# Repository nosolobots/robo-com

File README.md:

# robo-com
 
The aim of the project is to create basic robotic kits for contests and competitions. 
 
Currently, there are two kits in progress: 
 
> **linus_v1** a *line follower* robot  
> **taurus_v1** a *mini sumo* robot

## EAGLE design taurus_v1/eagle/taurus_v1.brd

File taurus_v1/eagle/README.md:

### *taurus_v1* PCB eagle files repository

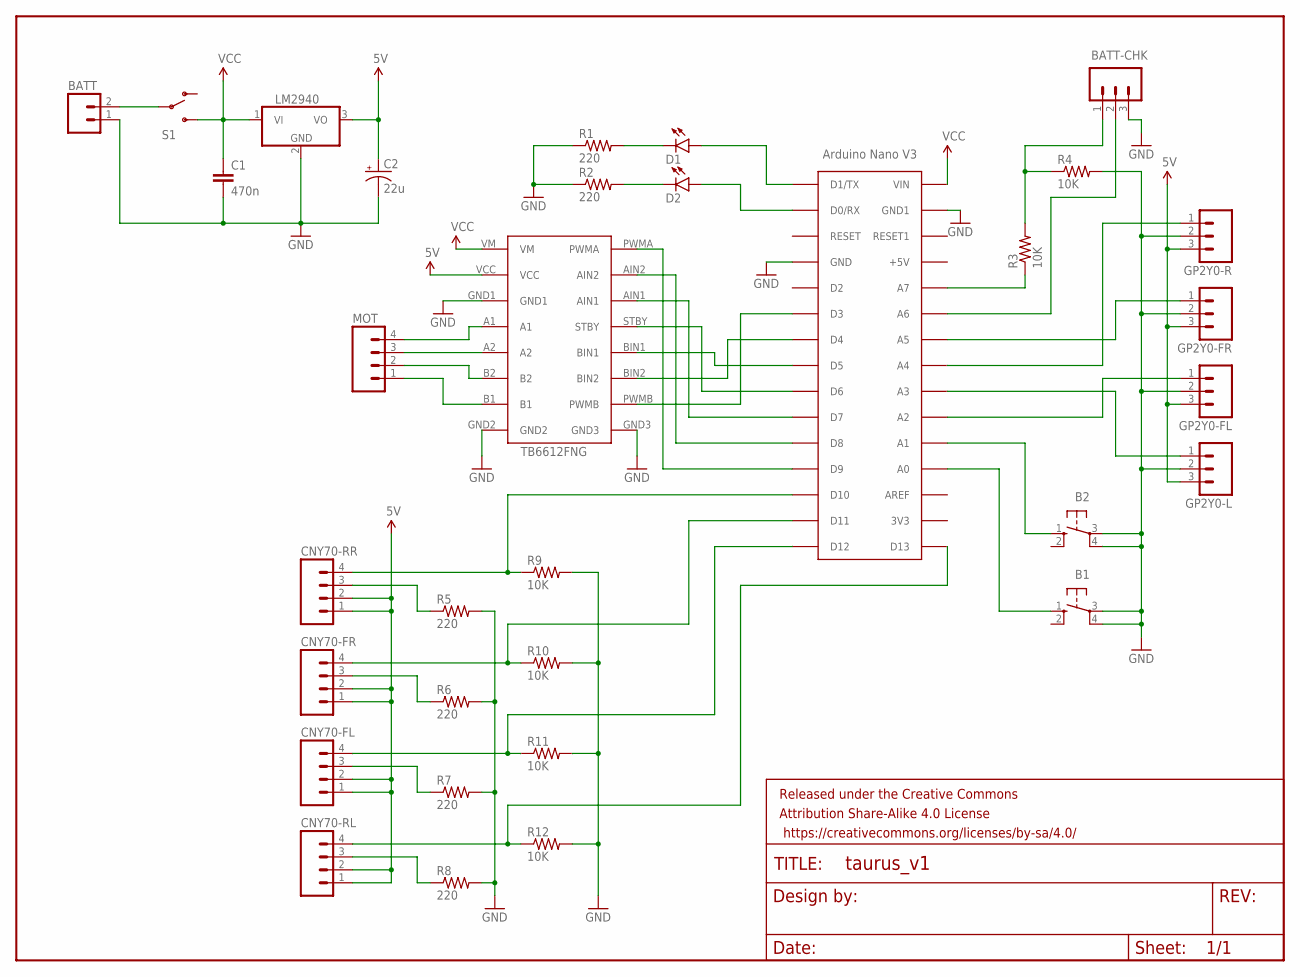
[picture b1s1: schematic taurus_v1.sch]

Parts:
B1, B2: 10-XX; B3F-10XX
BATT: M02PTH; 1X02
BATT-CHK: M03PTH; 1X03
C1: 470n; CAP-PTH-5MM
C2: 22u; CPOL-RADIAL-10UF-25V
CNY70-FL, CNY70-FR, CNY70-RL, CNY70-RR: M04PTH; 1X04
D1, D2: LED3MM
FRAME1: FRAME-LETTERNO_PACKAGE; DUMMY
GP2Y0-FL, GP2Y0-FR, GP2Y0-L, GP2Y0-R: M03PTH; 1X03
LM2940: 7805TV; TO220V
MOT: M04PTH; 1X04
R1, R2, R5, R6, R7, R8: 220; AXIAL-0.4
R3, R4, R9, R10, R11, R12: 10K; AXIAL-0.4
S1: SWITCH-SPDTPTH; SWITCH-SPDT
TB1: TB6612FNG
U$1: ARDUINONANO; PDIP-32

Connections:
5V: C2.1 (+), CNY70-FL.1, CNY70-FL.2, CNY70-FR.1, CNY70-FR.2, CNY70-RL.1, CNY70-RL.2, CNY70-RR.1, CNY70-RR.2, GP2Y0-FL.3, GP2Y0-FR.3, GP2Y0-L.3, GP2Y0-R.3, LM2940.3 (VO), TB1.VCC
GND: B1.3, B1.4 (P1), B2.3, B2.4 (P1), BATT.1, BATT-CHK.3, C1.2, C2.2 (-), GP2Y0-FL.2, GP2Y0-FR.2, GP2Y0-L.2, GP2Y0-R.2, LM2940.2 (GND), R1.P$1 (1), R2.P$1 (1), R4.P$2 (2), R5.P$2 (2), R6.P$2 (2), R7.P$2 (2), R8.P$2 (2), R9.P$2 (2), R10.P$2 (2), R11.P$2 (2), R12.P$2 (2), TB1.GND1, TB1.GND2, TB1.GND3, U$1.GND, U$1.GND1
unnamed: TB1.PWMA, U$1.D9
unnamed: TB1.AIN2, U$1.D8
unnamed: TB1.AIN1, U$1.D7
unnamed: TB1.STBY, U$1.D6
unnamed: TB1.BIN1, U$1.D5
unnamed: TB1.BIN2, U$1.D4
unnamed: TB1.PWMB, U$1.D3
unnamed: D1.K (C), R1.P$2 (2)
unnamed: D2.K (C), R2.P$2 (2)
unnamed: D2.A, U$1.D0/RX
unnamed: D1.A, U$1.D1/TX
unnamed: BATT.2, S1.2
unnamed: B1.1 (S), U$1.A7 (A0)
unnamed: B2.1 (S), U$1.A6 (A1)
unnamed: GP2Y0-L.1, U$1.A4 (A3)
unnamed: GP2Y0-R.1, U$1.A3 (A4)
unnamed: GP2Y0-FL.1, U$1.A5 (A2)
unnamed: BATT-CHK.2, U$1.A1 (A6)
unnamed: R3.P$1 (1), U$1.A0 (A7)
unnamed: BATT-CHK.1, R3.P$2 (2), R4.P$1 (1)
unnamed: MOT.4, TB1.A1
unnamed: MOT.3, TB1.A2
unnamed: MOT.2, TB1.B2
unnamed: MOT.1, TB1.B1
unnamed: CNY70-RR.4, R9.P$1 (1), U$1.D10
unnamed: CNY70-RR.3, R5.P$1 (1)
unnamed: CNY70-FR.3, R6.P$1 (1)
unnamed: CNY70-FL.3, R7.P$1 (1)
unnamed: CNY70-RL.3, R8.P$1 (1)
unnamed: CNY70-FR.4, R10.P$1 (1), U$1.D11
unnamed: CNY70-RL.4, R12.P$1 (1), U$1.D13
unnamed: CNY70-FL.4, R11.P$1 (1), U$1.D12
unnamed: GP2Y0-FR.1, U$1.A2 (A5)
VCC: C1.1, LM2940.1 (VI), S1.3 (S), TB1.VM, U$1.VIN

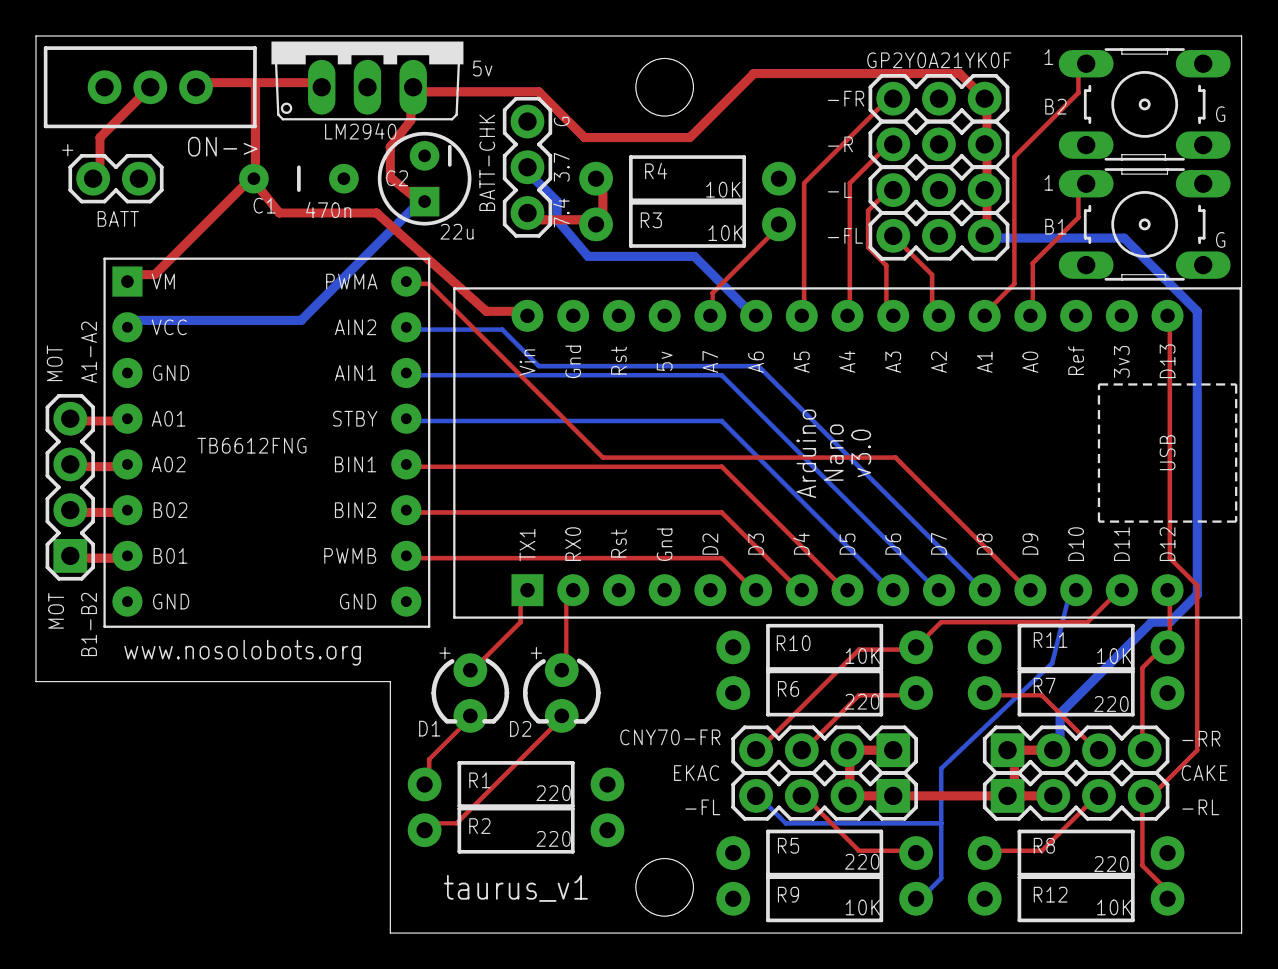
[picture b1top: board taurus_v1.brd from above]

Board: 2 copper layers, 67.0 x 49.8 mm, 34 parts (0 on the bottom side), 36 nets.

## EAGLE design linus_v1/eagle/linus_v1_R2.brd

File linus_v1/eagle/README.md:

### linus_v1 PCB eagle files repository

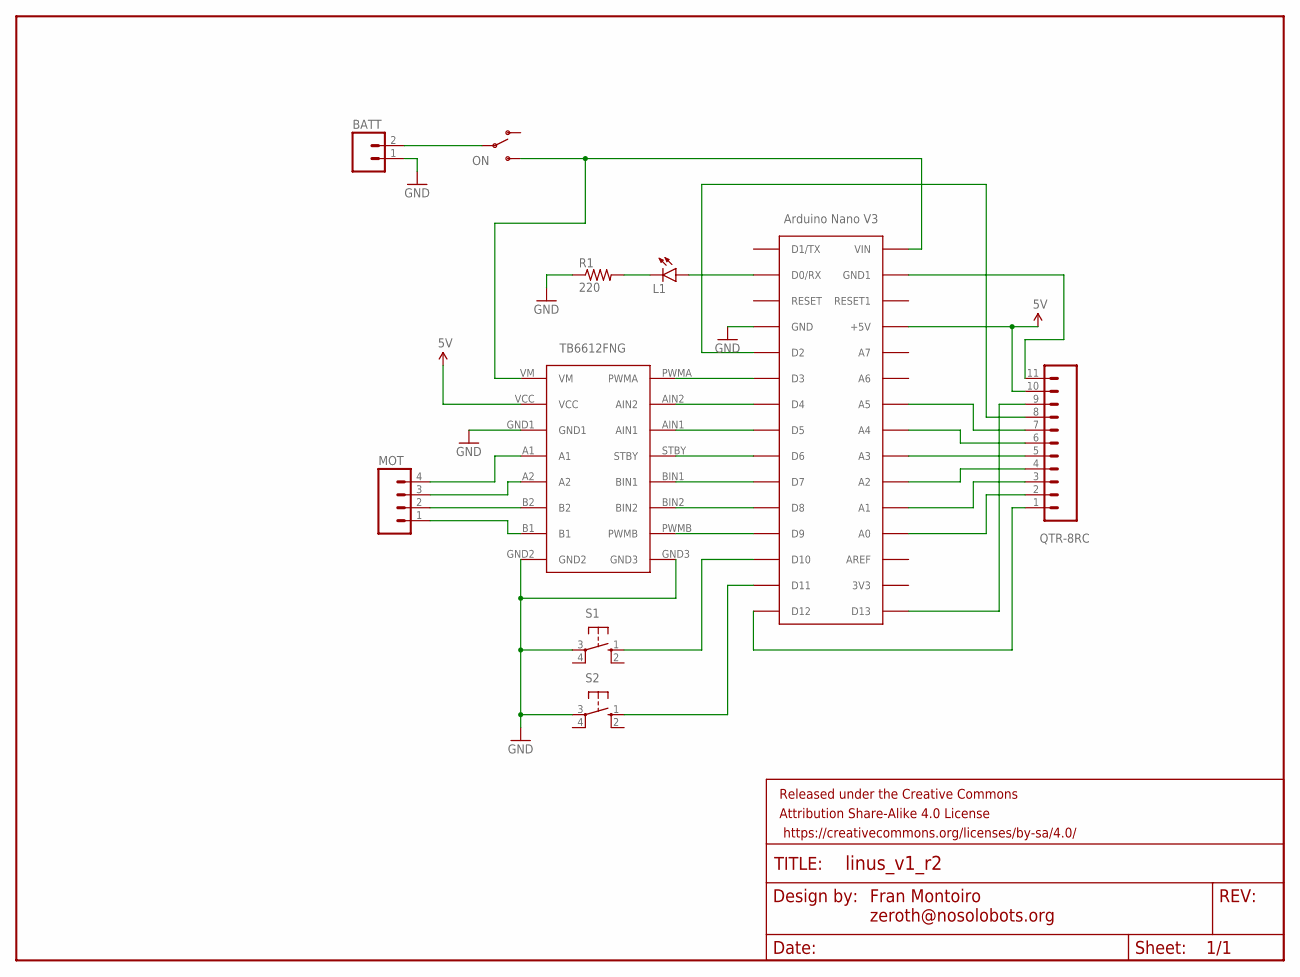
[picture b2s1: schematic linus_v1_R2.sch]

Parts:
BATT: M02PTH; 1X02
FRAME1: FRAME-LETTERNO_PACKAGE; DUMMY
L1: LED5MM
MOT: M04PTH; 1X04
ON: SWITCH-SPDTPTH; SWITCH-SPDT
QTR-8RC: M11PTH; 1X11
R1: 220; AXIAL-0.4
S1, S2: 10-XX; B3F-10XX
TB1: TB6612FNG
U$1: ARDUINONANO; PDIP-32

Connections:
5V: QTR-8RC.10, TB1.VCC, U$1.+5V
GND: BATT.1, R1.P$1 (1), S1.3, S2.3, TB1.GND1, TB1.GND2, TB1.GND3, U$1.GND
unnamed: MOT.4, TB1.A1
unnamed: MOT.3, TB1.A2
unnamed: MOT.2, TB1.B2
unnamed: MOT.1, TB1.B1
unnamed: QTR-8RC.8, U$1.D2
unnamed: S1.1 (S), U$1.D10
unnamed: S2.1 (S), U$1.D11
unnamed: TB1.PWMA, U$1.D3
unnamed: TB1.AIN2, U$1.D4
unnamed: TB1.AIN1, U$1.D5
unnamed: TB1.STBY, U$1.D6
unnamed: TB1.BIN1, U$1.D7
unnamed: TB1.BIN2, U$1.D8
unnamed: TB1.PWMB, U$1.D9
unnamed: QTR-8RC.7, U$1.A2 (A5)
unnamed: QTR-8RC.6, U$1.A3 (A4)
unnamed: QTR-8RC.5, U$1.A4 (A3)
unnamed: QTR-8RC.4, U$1.A5 (A2)
unnamed: QTR-8RC.3, U$1.A6 (A1)
unnamed: QTR-8RC.2, U$1.A7 (A0)
unnamed: QTR-8RC.1, U$1.D12
unnamed: ON.3 (S), TB1.VM, U$1.VIN
unnamed: L1.K (C), R1.P$2 (2)
unnamed: QTR-8RC.9, U$1.D13
unnamed: L1.A, U$1.D0/RX
unnamed: QTR-8RC.11, U$1.GND1
V+: BATT.2, ON.2

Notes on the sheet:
Fran Montoiro zeroth@nosolobots.org

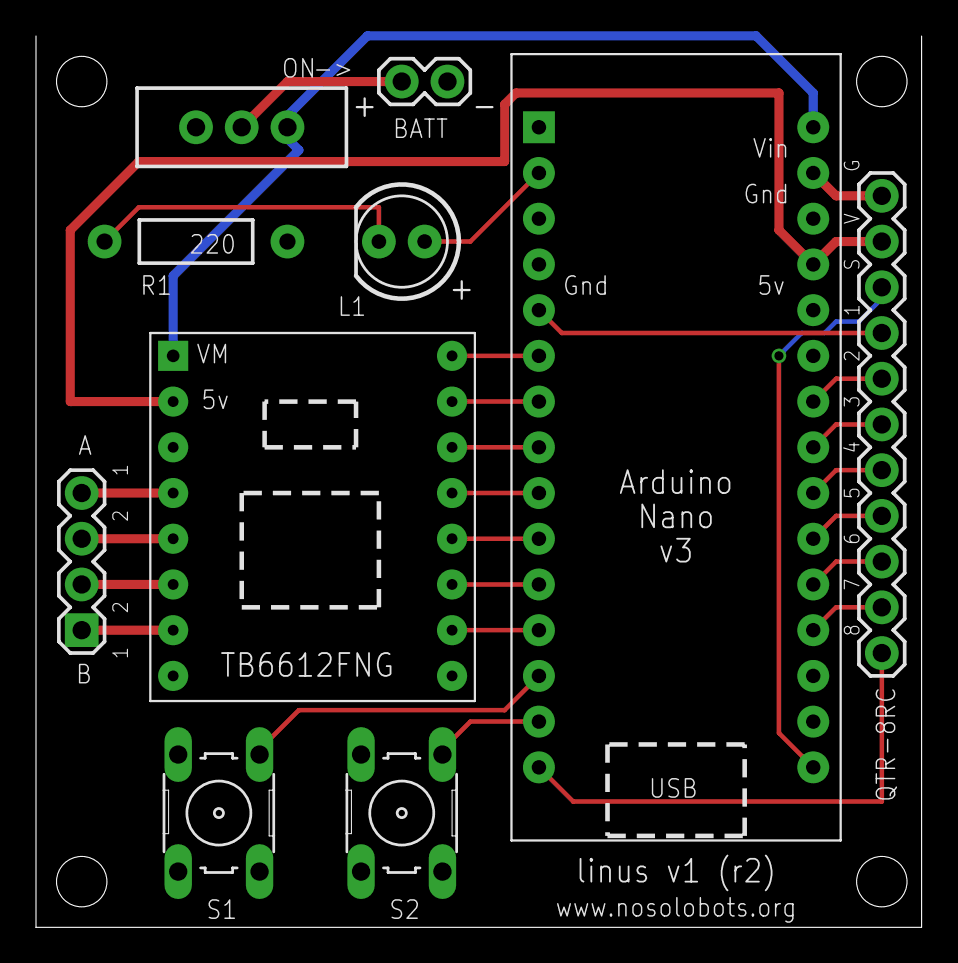
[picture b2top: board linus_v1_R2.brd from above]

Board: 2 copper layers, 49.2 x 49.5 mm, 11 parts (0 on the bottom side), 29 nets.

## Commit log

2017-03-11 Set theme jekyll-theme-cayman
2017-03-11 Create LICENSE
2017-03-11 Update LICENSE
2017-03-30 Rename REDME.md to README.md

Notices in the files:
parts and their libraries:
SparkFun-Connectors: Licensing: Creative Commons ShareAlike 4.0 International - https://creativecommons.org/licenses/by-sa/4.0
SparkFun-Aesthetics: Released under the Creative Commons Attribution Share-Alike 4.0 License
SparkFun-Aesthetics: https://creativecommons.org/licenses/by-sa/4.0
